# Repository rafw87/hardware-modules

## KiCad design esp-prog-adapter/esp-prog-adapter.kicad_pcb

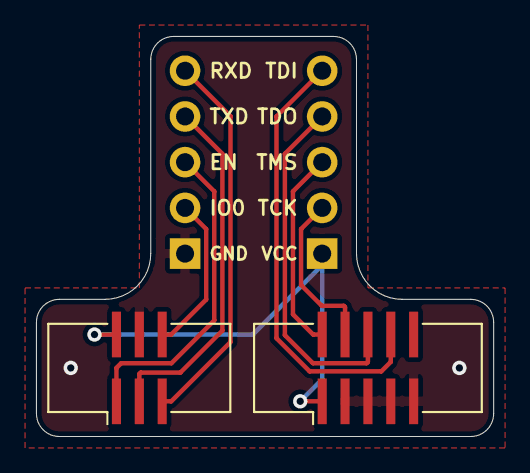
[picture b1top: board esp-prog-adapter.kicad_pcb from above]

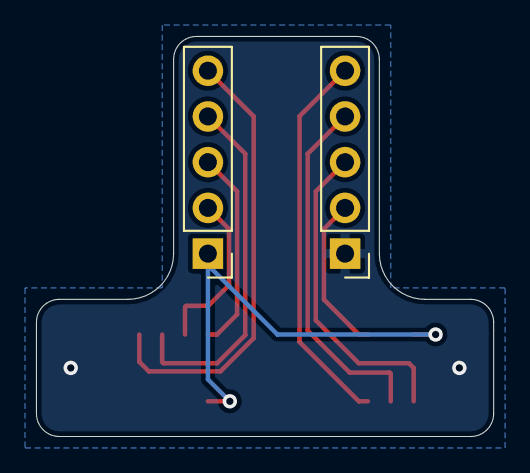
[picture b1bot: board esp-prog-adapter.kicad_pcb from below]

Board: 2 copper layers, 25.4 x 22.2 mm, 4 parts (2 on the bottom side), 10 nets.

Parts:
J1: Male IDC connector, 2x03, 1.27mm, SMD; IDC-Header_2x03_P1.27mm_Vertical_SMD
J2: Male IDC connector 2x05, 1.27mm, SMD; IDC-Header_2x05_P1.27mm_Vertical_SMD
J3, J4: Pin header 1x05, 2.54mm; PinHeader_1x05_P2.54mm_Vertical

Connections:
/EN: J1.1, J4.3
/IO0: J1.6, J4.2
/RXD: J1.5, J4.5
/TCK: J2.4, J3.2
/TDI: J2.8, J3.5
/TDO: J2.6, J3.4
/TMS: J2.2, J3.3
/TXD: J1.3, J4.4
GND: J1.4, J2.3, J2.5, J2.7, J2.9, J4.1
VCC: J1.2, J2.1, J3.1

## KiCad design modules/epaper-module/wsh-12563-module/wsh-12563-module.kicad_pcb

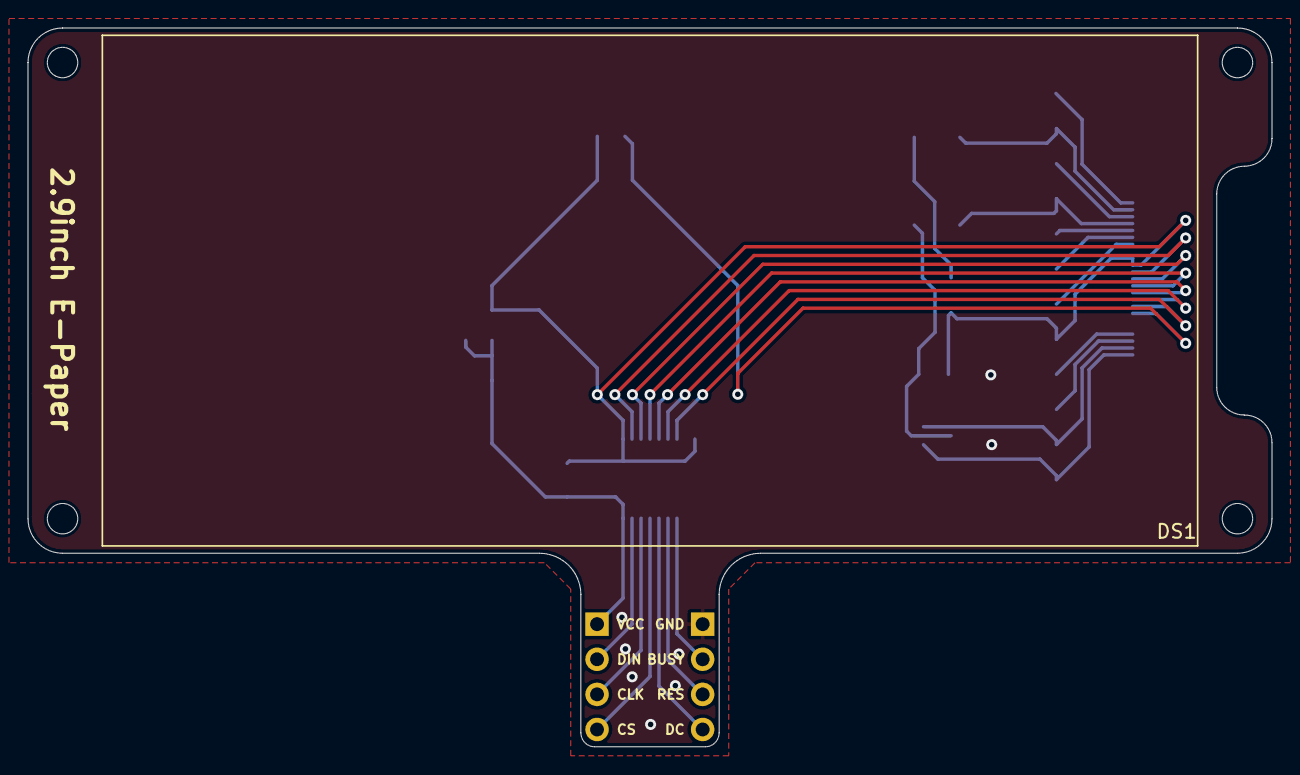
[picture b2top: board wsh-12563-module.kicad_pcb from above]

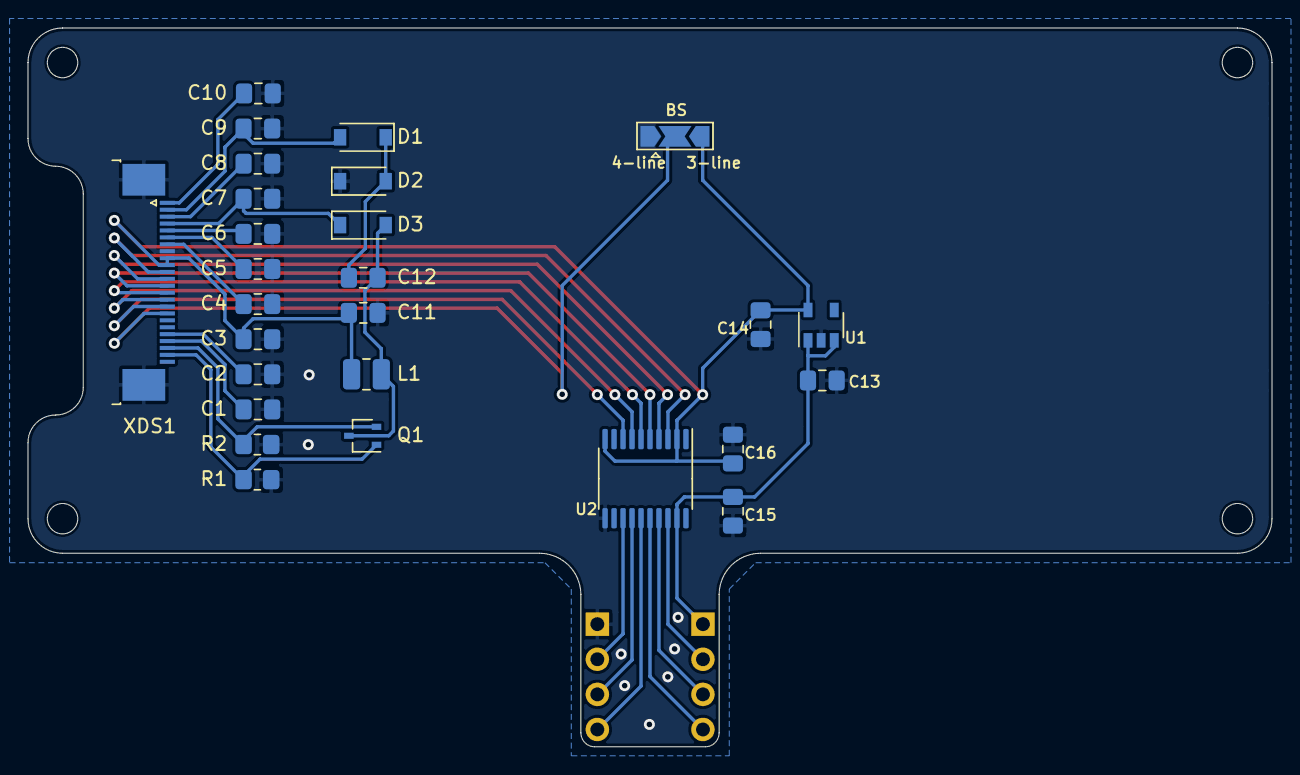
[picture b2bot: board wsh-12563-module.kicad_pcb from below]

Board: 2 copper layers, 90.0 x 52.0 mm, 34 parts (29 on the bottom side), 29 nets.

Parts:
C1, C2, C3, C4, C5, C6, C7, C8, C9, C10: 1u; C_0805_2012Metric_Pad1.18x1.45mm_HandSolder
C11, C12: 4.7u; C_0805_2012Metric_Pad1.18x1.45mm_HandSolder
C13: 10uF; C_0805_2012Metric_Pad1.18x1.45mm_HandSolder
C14: 4.7uF; C_0805_2012Metric_Pad1.18x1.45mm_HandSolder
C15, C16: 100nF; C_0805_2012Metric_Pad1.18x1.45mm_HandSolder
D1, D2, D3: MBR0530; D_SOD-123
DS1: WSH-12561; WSH-12563
H1, H2, H3, H4: MountingHole; MountingHole_2.2mm_M2
J1, J2: Conn_01x04; PinHeader_1x04_P2.54mm_Vertical
JP1: Jumper_NC_Dual; SolderJumper-3_P2.0mm_Open_TrianglePad1.0x1.5mm
L1: 10u; L_TYA252012
Q1: Si1308EDL; SOT-323_SC-70
R1: 10k; R_0805_2012Metric_Pad1.20x1.40mm_HandSolder
R2: 3R; R_0805_2012Metric_Pad1.20x1.40mm_HandSolder
U1: MIC5504-3.3YM5; SOT-23-5
U2: TXS0108EPW; TSSOP-20_4.4x6.5mm_P0.65mm
XDS1: WSH-12561-FFC-MP; TE_2-1734839-4_1x24-1MP_P0.5mm_Horizontal

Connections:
+3V3: C3.1, C11.1, C14.1, C16.1, JP1.3, L1.2, U1.5, U2.2, U2.10, XDS1.9, XDS1.10
/BS: JP1.2, XDS1.17
/BUSY: J1.2, U2.13
/BUSY': U2.8, XDS1.16
/CLK: J2.3, U2.17
/CLK': U2.4, XDS1.12
/CS: J2.4, U2.16
/CS': U2.5, XDS1.13
/DC: J1.4, U2.15
/DC': U2.6, XDS1.14
/DIN: J2.2, U2.18
/DIN': U2.3, XDS1.11
/Display/GDR: Q1.1, R1.1, XDS1.23
/Display/PREVGH: C7.1, D3.1, XDS1.4
/Display/PREVGL: C9.1, D1.2, XDS1.2
/Display/RESE: Q1.2, R2.1, XDS1.22
/Display/VCOM: C10.1, XDS1.1
/Display/VDD: C4.1, XDS1.7
/Display/VPP: C5.1, XDS1.6
/Display/VSH1: C6.1, XDS1.5
/Display/VSH2: C2.1, XDS1.20
/Display/VSL: C8.1, XDS1.3
/RES: J1.3, U2.14
/RES': U2.7, XDS1.15
GND: C1.2, C2.2, C3.2, C4.2, C5.2, C6.2, C7.2, C8.2, C9.2, C10.2, C11.2, C13.2, C14.2, C15.2, C16.2, D2.1, J1.1, JP1.1, R1.2, R2.2, U1.2, U2.11, XDS1.8, XDS1.MP
unnamed: C1.1, XDS1.21
unnamed: C12.1, D1.1, D2.2
unnamed: C12.2, D3.2, L1.1, Q1.3
VCC: C13.1, C15.1, J2.1, U1.1, U1.3, U2.19
